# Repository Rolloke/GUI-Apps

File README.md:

# GUI-Apps
This repository contains Qt Projects for several scopes

### GitView 

App providing tools to work with git repositories.
- works with Qt5 and Qt6
- displays a tree containing files and status of files
  - visibility of the file may depend on status
- editing text files
- editing of binary files
- search of text
  - in single text
  - in textfiles contained by a selected folder and subfolders
  - in all tree views
- preview of html and markdown files
- shows difference of text files
  - supports several diff and merge tools
  - difference between branches
  - merge branches with external tools (meld, etc)
- shows history
- shows stash list
- shows blame
- shows branches

### RaspiMediaList

Kodi media list viewer and editor

- Test TV or Radio channels instantly with media viewer / player.
- supports also reply with other players like ***VLC***
- Shows media info of streamed data
  - works better with Qt5 than with Qt6
- Stores TV or Radio channels from m3u files as favorites for usage within raspberry kodi.  
- Supports upload to and download from raspberry kodi. 

### Oscilloscope 

Oscilloscope and **function** generator for selectable audio devices on sound card of a PC (Qt5)

- Calibration of single channels regarding offset and amplification
- Supports also probes with different amplification
- Support several trigger functions
- FFT with filter functions
- Mathematical function for combining channels
- Cursors

### RecentFilesList

Program to edit recent files list of Linux Ubuntu

- Opens files from List
- Removes entries from list
- Stores changed entries into list 

#### Warranty

These programs are provided AS IS with NO WARRANTY OF ANY KIND

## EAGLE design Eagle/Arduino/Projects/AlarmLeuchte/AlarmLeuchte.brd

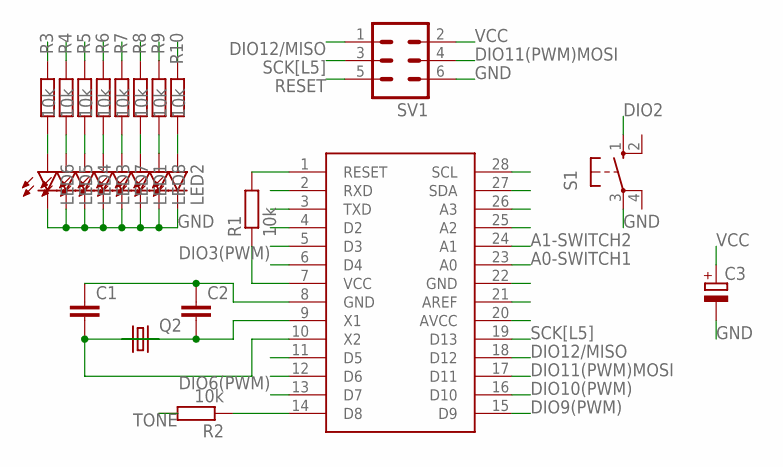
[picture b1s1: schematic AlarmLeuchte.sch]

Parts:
C1, C2: C-EU025-024X044; C025-024X044
C3: CPOL-EUE3.5-8; E3,5-8
LED1, LED2, LED3, LED4, LED5, LED6, LED7, LED8: LED5MM
Q2: CRYSTALHC49S; HC49/S
R1: 10k; 0207/15
R2, R3, R4, R5, R6, R7, R8, R9: 10k; 0207/10
R10: 10k; 0204/7
S1: 10-XX; B3F-10XX
SV1: MA03-2
U$1: ATMEGA328P-PU; DIL28-3

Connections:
A0-SWITCH1: U$1.23 (A0)
A1-SWITCH2: U$1.24 (A1)
A3: U$1.26 (A3)
A4[SDA]: U$1.27 (SDA)
A5[SCL]: R9.1, U$1.28 (SCL)
AREF: U$1.21 (AREF)
DIO1(TX): U$1.3 (TXD)
DIO2: S1.1 (S), U$1.4 (D2), U$1.25 (A2)
DIO3(PWM): R8.1, U$1.5 (D3)
DIO4: R7.1, U$1.6 (D4)
DIO5(PWM): R5.1, U$1.11 (D5)
DIO6(PWM): R10.1, U$1.12 (D6)
DIO7: R3.1, U$1.13 (D7)
DIO8: R2.1, U$1.14 (D8)
DIO9(PWM): R4.1, U$1.15 (D9)
DIO10(PWM): R6.1, U$1.16 (D10)
DIO11(PWM)MOSI: SV1.4, U$1.17 (D11)
DIO12/MISO: SV1.1, U$1.18 (D12)
DPIO0(RX): U$1.2 (RXD)
GND: C1.1, C2.1, C3.-, LED1.K (C), LED2.K (C), LED3.K (C), LED4.K (C), LED5.K (C), LED6.K (C), LED7.K (C), LED8.K (C), S1.3, SV1.6, U$1.8 (GND), U$1.22 (GND)
unnamed: LED6.A, R3.2
unnamed: LED5.A, R4.2
unnamed: LED4.A, R5.2
unnamed: LED3.A, R6.2
unnamed: LED7.A, R7.2
unnamed: LED1.A, R8.2
unnamed: LED8.A, R9.2
unnamed: LED2.A, R10.2
RESET: R1.2, SV1.5, U$1.1 (RESET)
SCK[L5]: SV1.3, U$1.19 (D13)
TONE: R2.2
VCC: C3.+, R1.1, SV1.2, U$1.7 (VCC), U$1.20 (AVCC)
X1: C2.2, Q2.1, U$1.9 (X1)
X2: C1.2, Q2.2, U$1.10 (X2)

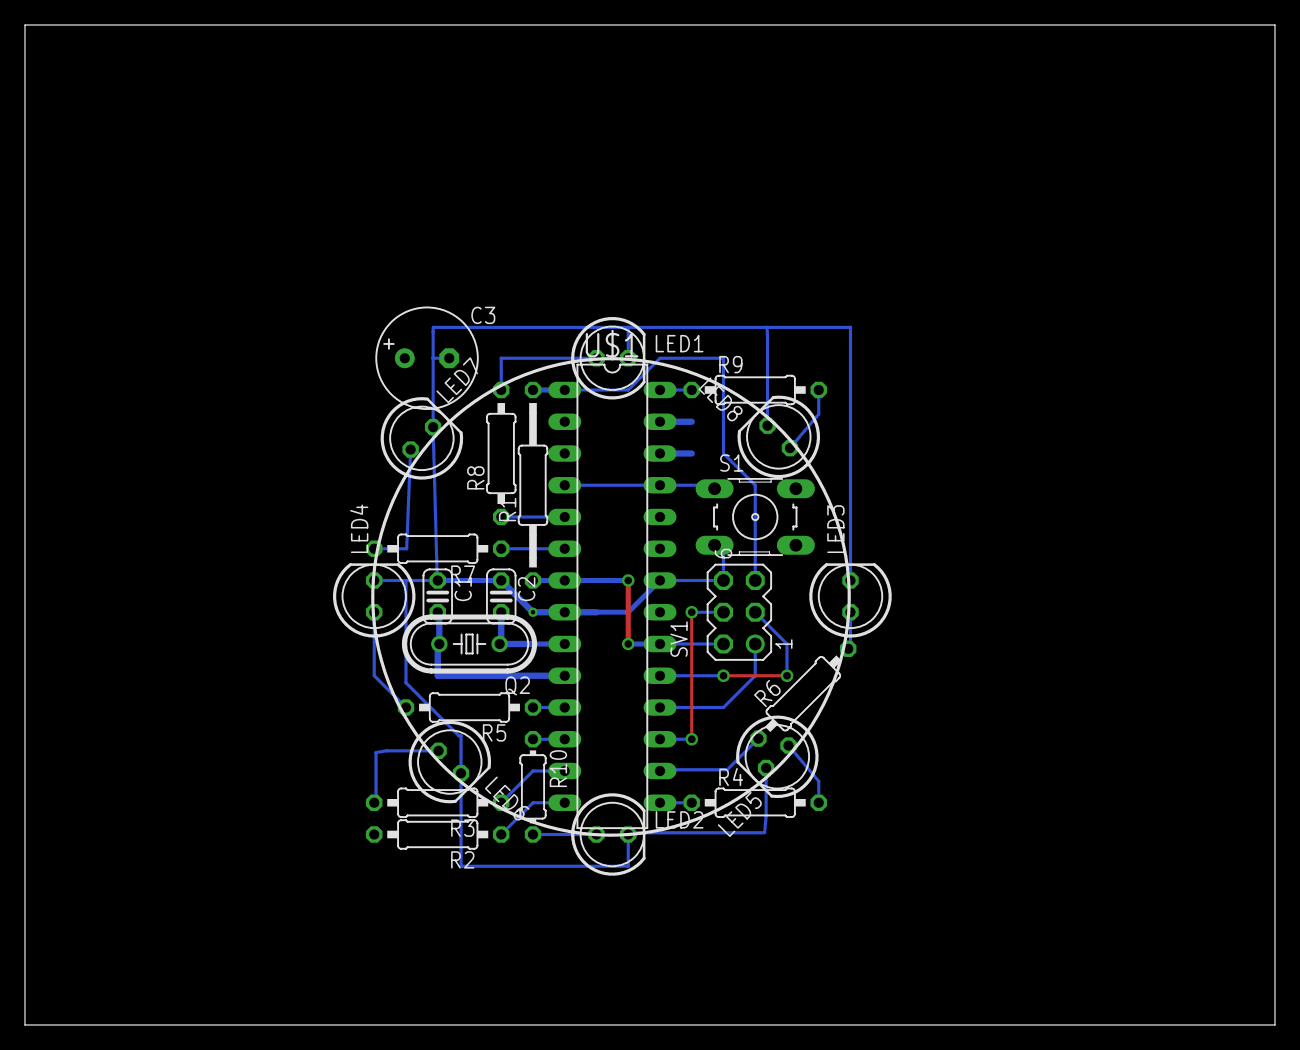
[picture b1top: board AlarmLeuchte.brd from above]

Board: 2 copper layers, 100.0 x 80.0 mm, 25 parts (0 on the bottom side), 26 nets.

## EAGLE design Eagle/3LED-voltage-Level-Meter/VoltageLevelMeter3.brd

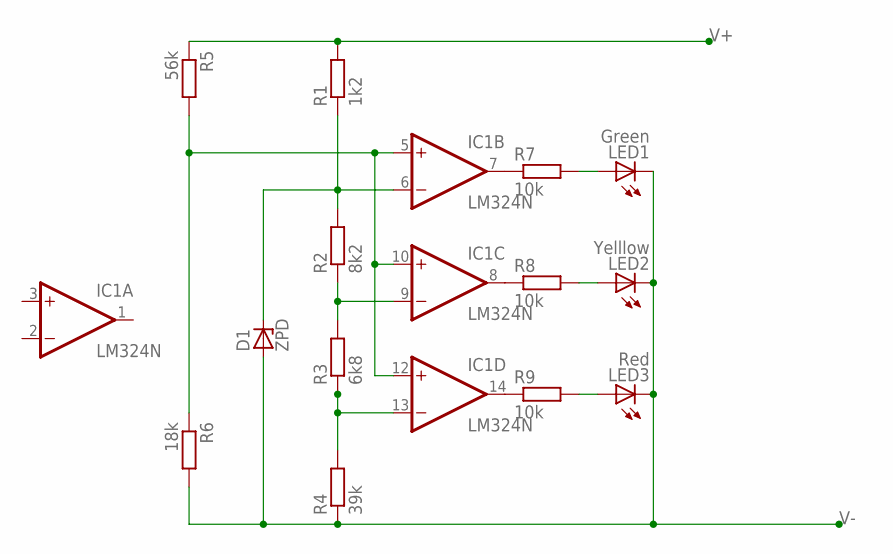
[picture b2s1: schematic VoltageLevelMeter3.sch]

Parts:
D1: ZPD; DO35Z10
IC1: LM324N; DIL14
LED1: Green; LED3MM
LED2: Yelllow; LED3MM
LED3: Red; LED3MM
R1: 1k2; 0207/7
R2: 8k2; 0207/7
R3: 6k8; 0207/7
R4: 39k; 0207/7
R5: 56k; 0207/7
R6: 18k; 0207/7
R7, R8, R9: 10k; 0207/7

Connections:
unnamed: D1.C, IC1.6 (-IN), R1.1, R2.2
unnamed: IC1.9 (-IN), R2.1, R3.2
unnamed: IC1.13 (-IN), R3.1, R4.2
unnamed: IC1.14 (OUT), R9.1
unnamed: IC1.8 (OUT), R8.1
unnamed: IC1.7 (OUT), R7.1
unnamed: IC1.5 (+IN), IC1.10 (+IN), IC1.12 (+IN), R5.2, R6.1
unnamed: LED1.A, R7.2
unnamed: LED2.A, R8.2
unnamed: LED3.A, R9.2
V+: IC1.4 (V+), R1.2, R5.1
V-: D1.A, IC1.11 (V-), LED1.K (C), LED2.K (C), LED3.K (C), R4.1, R6.2

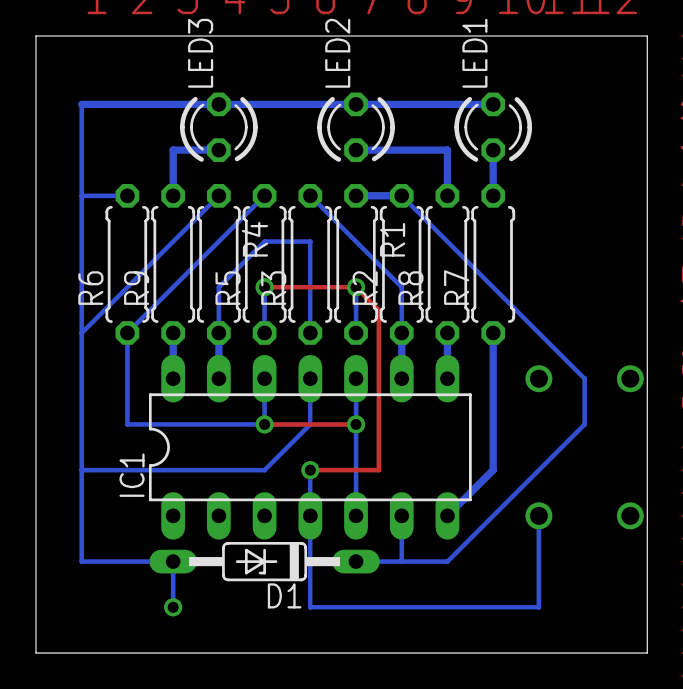
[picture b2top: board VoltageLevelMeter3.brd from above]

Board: 2 copper layers, 34.0 x 34.3 mm, 14 parts (0 on the bottom side), 12 nets.

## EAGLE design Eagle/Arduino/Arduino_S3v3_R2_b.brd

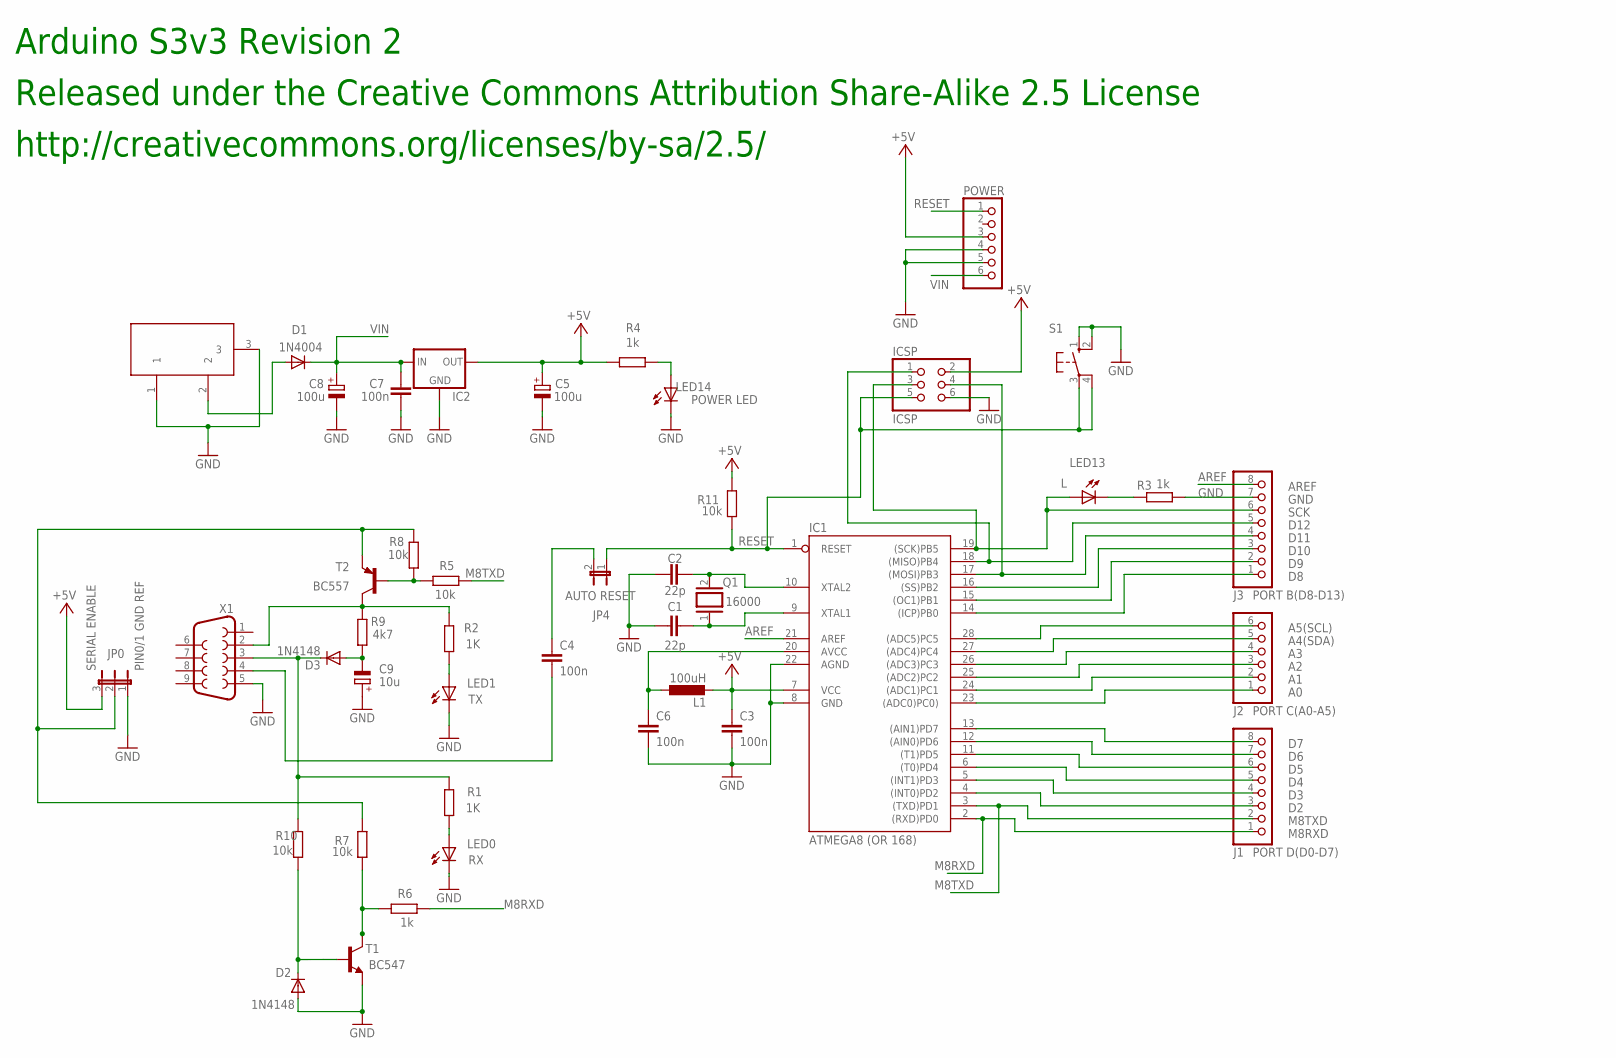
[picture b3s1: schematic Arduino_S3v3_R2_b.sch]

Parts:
C1, C2: 22p; C025-024X044
C3, C4, C6, C7: 100n; C050-025X075
C5, C8: 100u; E3,5-8
C9: 10u; E5-6
D1: 1N4004; DO41-10
D2, D3: 1N4148; DO35-10
DC1: DC21MMX; DC-21MM
IC1: ATMEGA8 (OR 168); DIL28-3
IC2: 78XXL
ICSP: ICSP; 2X03
J1: PORT D(D0-D7); 1X08
J2: PORT C(A0-A5); 1X06
J3: PORT B(D8-D13); 1X08
JP0: JP2W
JP4: AUTO RESET; JP1W
L1: 100uH; 0204/5
LED0: RX; LED3MM
LED1: TX; LED3MM
LED13: L; LED3MM
LED14: POWER LED; LED3MM
POWER: PINHD-1X6; 1X06
Q1: 16000; QS
R1, R2: 1K; 0207/10
R3, R4, R6: 1k; 0207/10
R5, R7, R8, R10, R11: 10k; 0207/10
R9: 4k7; 0207/10
S1: 10-XX; B3F-10XX
T1: BC547; TO92
T2: BC557; TO92-EBC
X1: F09H

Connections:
+5V: C3.1, C5.+, IC1.7 (VCC), IC2.OUT, ICSP.2, JP0.3, L1.2, POWER.3, R4.2, R11.2
A0: IC1.23 ((ADC0)PC0)), J2.1
A1: IC1.24 ((ADC1)PC1), J2.2
A2: IC1.25 ((ADC2)PC2), J2.3
A3: IC1.26 ((ADC3)PC3), J2.4
A4(SDA): IC1.27 ((ADC4)PC4), J2.5
A5(SCL): IC1.28 ((ADC5)PC5), J2.6
AREF: IC1.21 (AREF), J3.8
D2: IC1.4 ((INT0)PD2), J1.3
D3: IC1.5 ((INT1)PD3), J1.4
D4: IC1.6 ((T0)PD4), J1.5
D5: IC1.11 ((T1)PD5), J1.6
D6: IC1.12 ((AIN0)PD6), J1.7
D7: IC1.13 ((AIN1)PD7), J1.8
D8: IC1.14 ((ICP)PB0), J3.1
D9: IC1.15 ((OC1)PB1), J3.2
D10: IC1.16 ((SS)PB2), J3.3
D11: IC1.17 ((MOSI)PB3), ICSP.4, J3.4
D12: IC1.18 ((MISO)PB4), ICSP.1, J3.5
GND: C1.1, C2.1, C3.2, C5.-, C6.2, C7.1, C8.-, C9.+, D2.A, DC1.1, DC1.3, IC1.8 (GND), IC1.22 (AGND), IC2.GND, ICSP.6, J3.7, JP0.1, LED0.K (C), LED1.K (C), LED14.K (C), POWER.4, POWER.5, R3.1, S1.1 (S), S1.2 (S1), T1.1 (E), X1.5
M8RXD: IC1.2 ((RXD)PD0), J1.1, R6.1
M8TXD: IC1.3 ((TXD)PD1), J1.2, R5.1
unnamed: C9.-, D3.A, R9.1
unnamed: LED14.A, R4.1
unnamed: C1.2, IC1.9 (XTAL1), Q1.1
unnamed: C2.2, IC1.10 (XTAL2), Q1.2
unnamed: D1.A, DC1.2
unnamed: D3.C, R1.2, R10.2, X1.3
unnamed: R6.2, R7.1, T1.3 (C)
unnamed: R5.2, R8.2, T2.B
unnamed: D2.C, R10.1, T1.2 (B)
unnamed: LED13.K (C), R3.2
unnamed: LED1.A, R2.1
unnamed: LED0.A, R1.1
unnamed: C4.1, JP4.2
unnamed: C4.2, X1.4
unnamed: R2.2, R9.2, T2.C, X1.2
unnamed: C6.1, IC1.20 (AVCC), L1.1
RESET: IC1.1 (RESET), ICSP.5, JP4.1, POWER.1, R11.1, S1.3, S1.4 (P1)
SCK: IC1.19 ((SCK)PB5), ICSP.3, J3.6, LED13.A
SERIAL_VCC: JP0.2, R7.2, R8.1, T2.E
VIN: C7.2, C8.+, D1.C, IC2.IN, POWER.6

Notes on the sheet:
PIN0/1 GND REF
SERIAL ENABLE
Released under the Creative Commons Attribution Share-Alike 2.5 License
http://creativecommons.org/licenses/by-sa/2.5/
Arduino S3v3 Revision 2

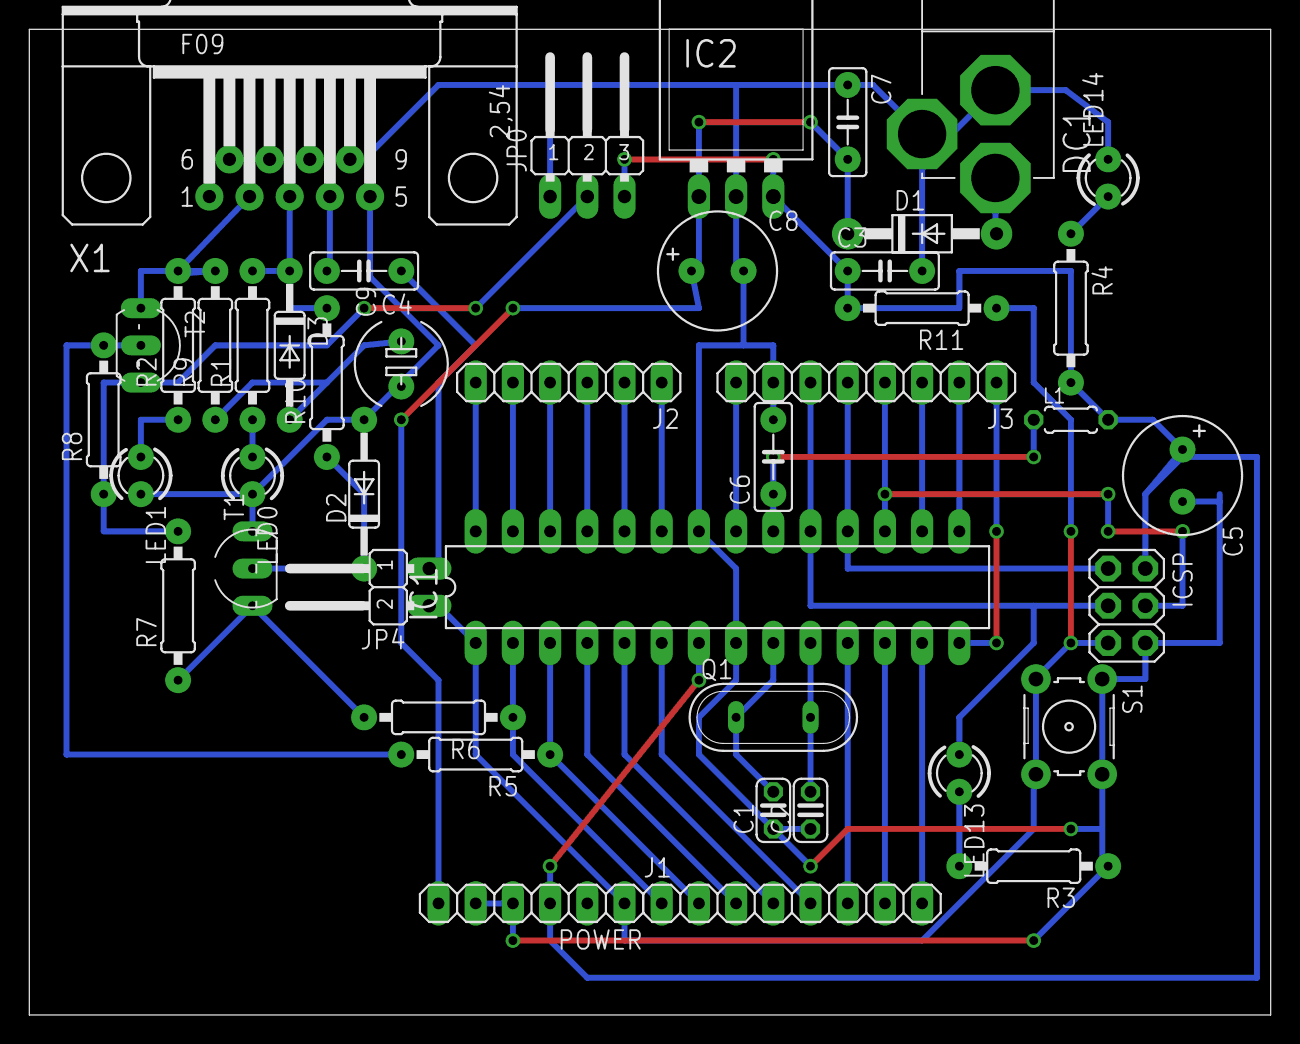
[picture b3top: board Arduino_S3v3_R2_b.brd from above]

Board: 2 copper layers, 84.8 x 67.3 mm, 43 parts (0 on the bottom side), 42 nets.

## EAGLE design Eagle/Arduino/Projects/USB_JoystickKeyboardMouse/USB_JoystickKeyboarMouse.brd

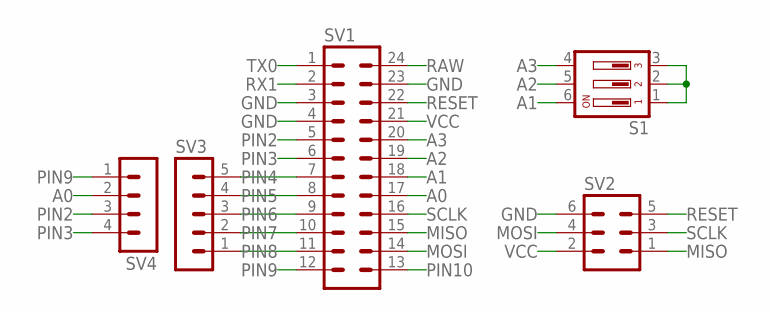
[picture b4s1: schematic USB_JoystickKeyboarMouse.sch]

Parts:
S1: DIP03YL
SV1: IC24P
SV2: MA03-2
SV3: MA05-1
SV4: MA04-1

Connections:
A0: SV1.17, SV4.2
A1: S1.6, SV1.18
A2: S1.5, SV1.19
A3: S1.4, SV1.20
GND: S1.1, S1.2, S1.3, SV1.3, SV1.4, SV1.23, SV2.6
MISO: SV1.15, SV2.1
MOSI: SV1.14, SV2.4
PIN2: SV1.5, SV4.3
PIN3: SV1.6, SV4.4
PIN4: SV1.7, SV3.5
PIN5: SV1.8, SV3.4
PIN6: SV1.9, SV3.3
PIN7: SV1.10, SV3.2
PIN8: SV1.11, SV3.1
PIN9: SV1.12, SV4.1
PIN10: SV1.13
RAW: SV1.24
RESET: SV1.22, SV2.5
RX1: SV1.2
SCLK: SV1.16, SV2.3
TX0: SV1.1
VCC: SV1.21, SV2.2

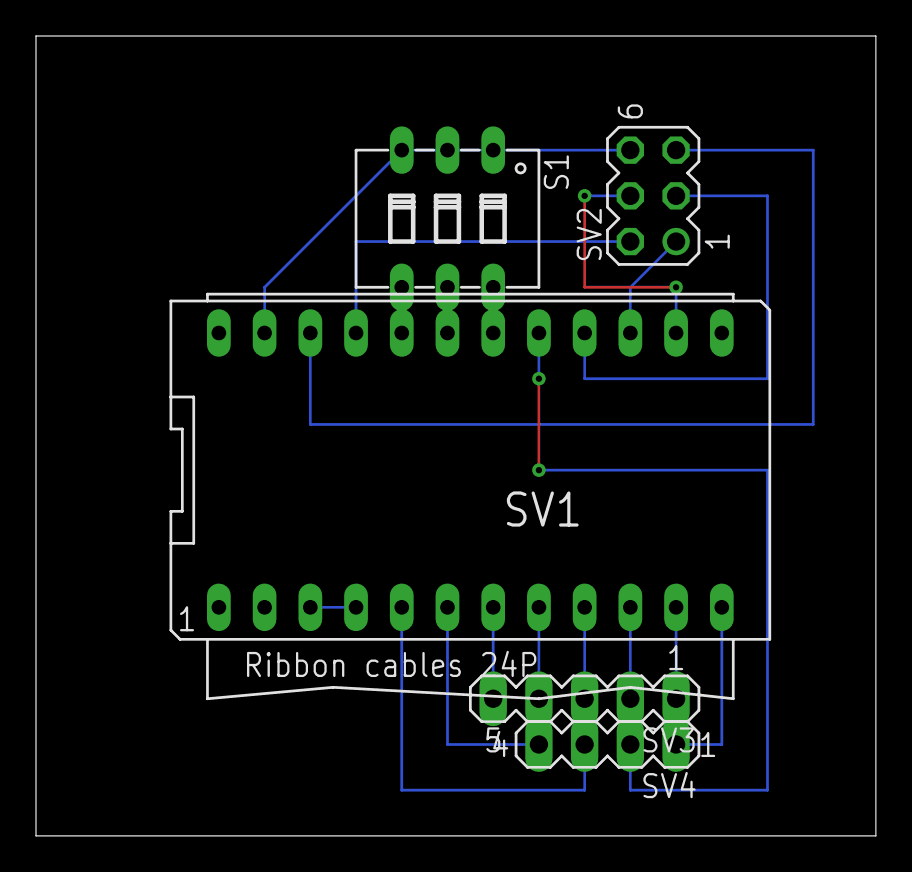
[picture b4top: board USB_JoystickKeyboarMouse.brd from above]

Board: 2 copper layers, 46.7 x 44.4 mm, 5 parts (0 on the bottom side), 18 nets.

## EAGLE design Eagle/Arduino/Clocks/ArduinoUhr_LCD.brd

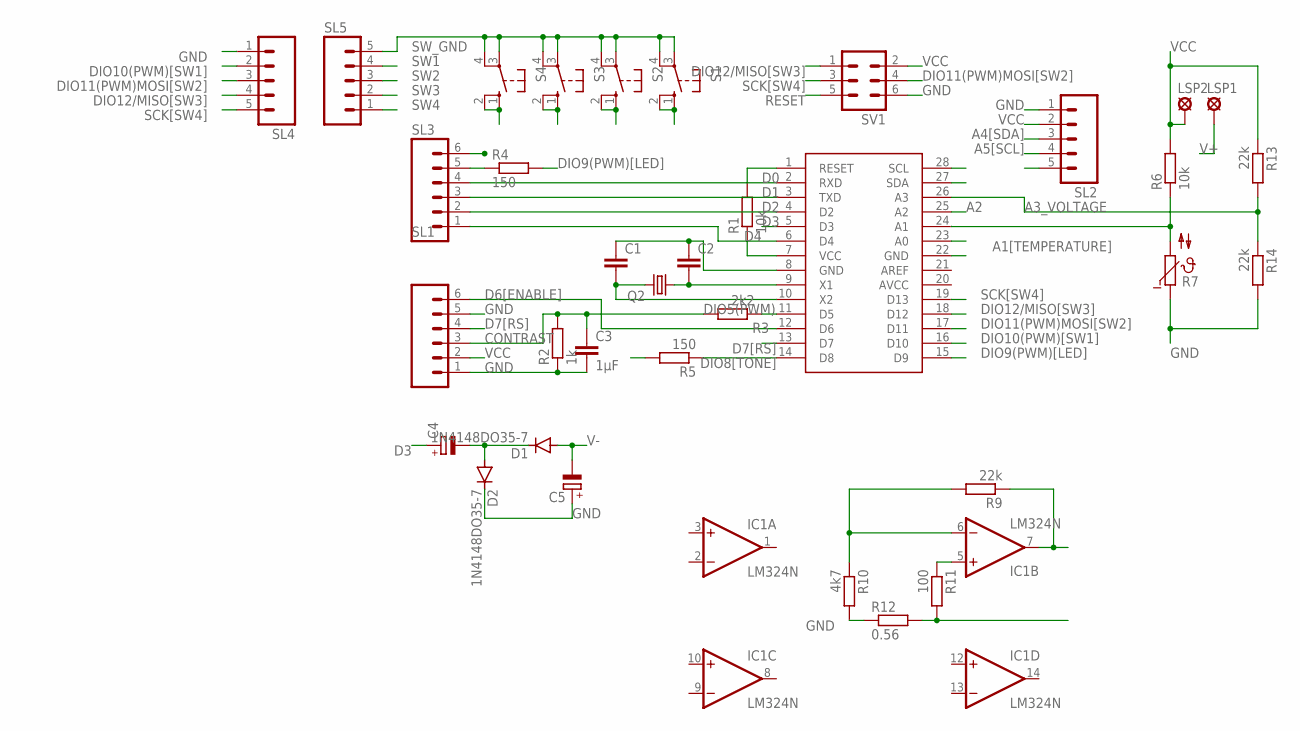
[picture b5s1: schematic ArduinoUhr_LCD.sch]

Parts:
C1, C2: C-EU025-024X044; C025-024X044
C3: 1µF; C050-024X044
C4, C5: CPOL-EUE2-5; E2-5
D1, D2: 1N4148DO35-7; DO35-7
IC1: LM324N; DIL14
LSP1, LSP2: LSP10
Q2: CRYSTALHC49S; HC49/S
R1: 10k; 0207/15
R2: 1k; 0204/7
R3: 2k2; 0204/7
R4: 150; 0207/10
R5: 150; 0204/7
R6: 10k; 0207/10
R7: NTC640-9; N640
R9, R13, R14: 22k; 0204/7
R10: 4k7; 0204/7
R11: 100; 0204/7
R12: 0.56; P0613/15
S1, S2, S3, S4: 10-XX; B3F-10XX
SL1, SL3: M06; 06P
SL2, SL4, SL5: M05; 05P
SV1: MA03-2
U$1: ATMEGA328P-PU; DIL28-3

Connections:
A0[CURRENT]: IC1.7 (OUT), R9.1, U$1.23 (A0)
A1[TEMPERATURE]: R6.1, R7.2, U$1.24 (A1)
A2: U$1.25 (A2)
A3_VOLTAGE: R13.2, R14.1, U$1.26 (A3)
A4[SDA]: SL2.3, U$1.27 (SDA)
A5[SCL]: SL2.4, U$1.28 (SCL)
CONTRAST: C3.1, R2.2, R3.2, SL1.3
D0: SL3.4, U$1.2 (RXD)
D1: SL3.3, U$1.3 (TXD)
D2: SL3.2, U$1.4 (D2)
D3: C4.+, U$1.5 (D3)
D4: SL3.1, U$1.6 (D4)
D6[ENABLE]: SL1.6, U$1.12 (D6)
D7[RS]: SL1.4, U$1.13 (D7)
DIO5(PWM): R3.1, U$1.11 (D5)
DIO8[TONE]: R5.1, U$1.14 (D8)
DIO9(PWM)[LED]: R4.2, U$1.15 (D9)
DIO10(PWM)[SW1]: SL4.2, U$1.16 (D10)
DIO11(PWM)MOSI[SW2]: SL4.3, SV1.4, U$1.17 (D11)
DIO12/MISO[SW3]: SL4.4, SV1.1, U$1.18 (D12)
GND: C1.1, C2.1, C3.2, C5.+, D2.C, R2.1, R7.1, R10.2, R12.1, R14.2, SL1.1, SL1.5, SL2.1, SL3.6, SL4.1, SV1.6, U$1.8 (GND), U$1.22 (GND)
unnamed: IC1.6 (-IN), R9.2, R10.1
unnamed: R4.1, SL3.5
unnamed: C4.-, D1.C, D2.A
unnamed: IC1.5 (+IN), R11.1
unnamed: R11.2, R12.2
RESET: R1.2, SV1.5, U$1.1 (RESET)
SCK[SW4]: SL4.5, SV1.3, U$1.19 (D13)
SW1: S4.1 (S), S4.2 (S1), SL5.4
SW2: S3.1 (S), S3.2 (S1), SL5.3
SW3: S2.1 (S), S2.2 (S1), SL5.2
SW4: S1.1 (S), S1.2 (S1), SL5.1
SW_GND: S1.3, S1.4 (P1), S2.3, S2.4 (P1), S3.3, S3.4 (P1), S4.3, S4.4 (P1), SL5.5
TONE: R5.2
V+: IC1.4 (V+), LSP1.MP
V-: C5.-, D1.A, IC1.11 (V-)
VCC: LSP2.MP, R1.1, R6.2, R13.1, SL1.2, SL2.2, SV1.2, U$1.7 (VCC)
X1: C2.2, Q2.1, U$1.9 (X1)
X2: C1.2, Q2.2, U$1.10 (X2)

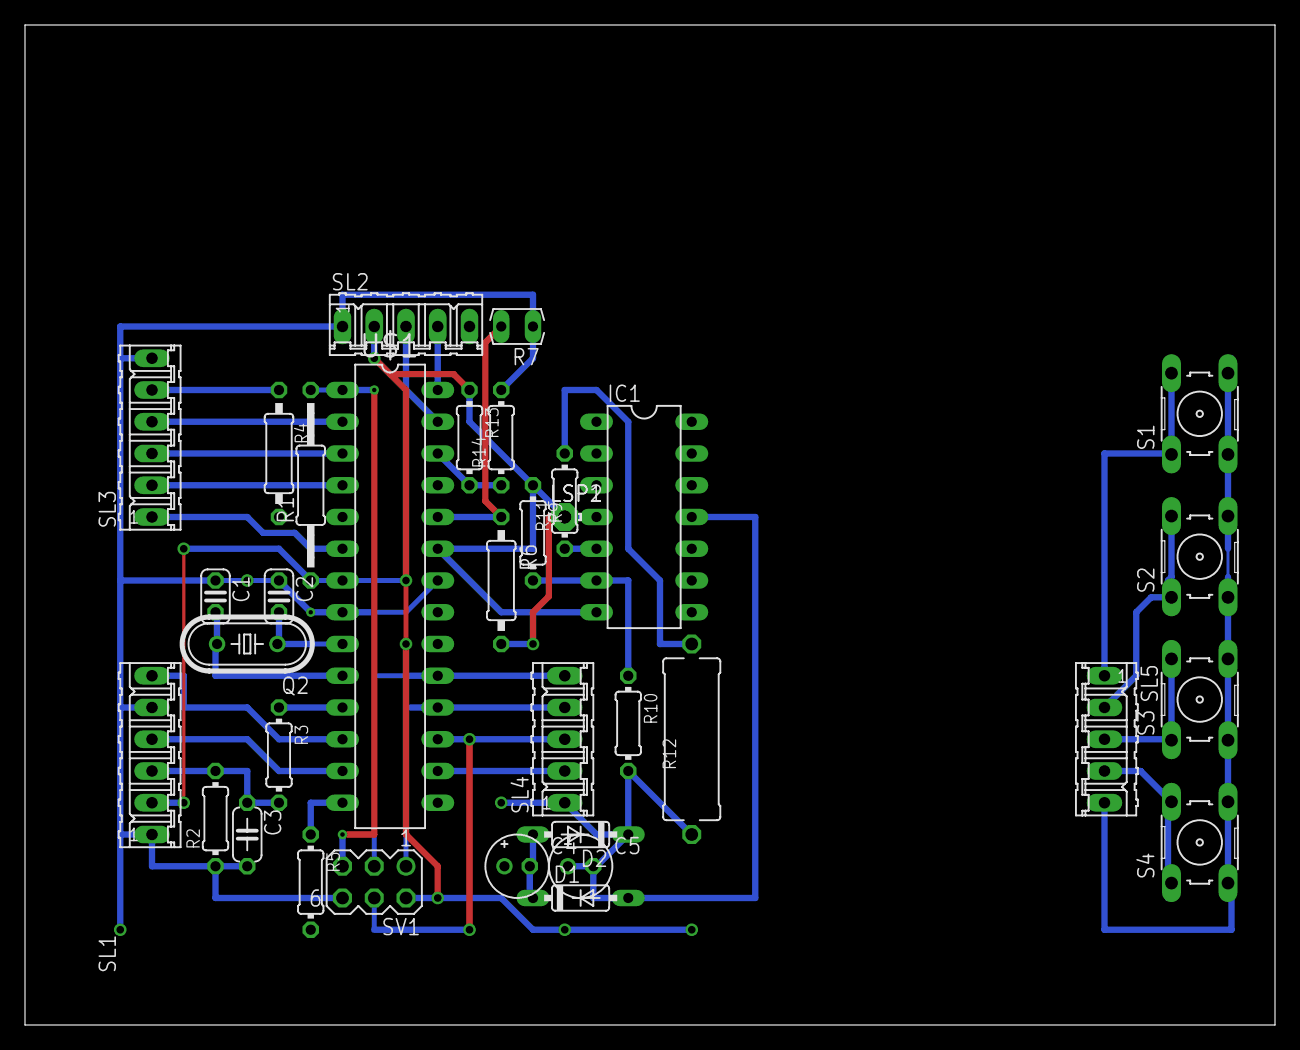
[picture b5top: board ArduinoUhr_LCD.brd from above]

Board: 2 copper layers, 100.0 x 80.0 mm, 35 parts (0 on the bottom side), 37 nets.

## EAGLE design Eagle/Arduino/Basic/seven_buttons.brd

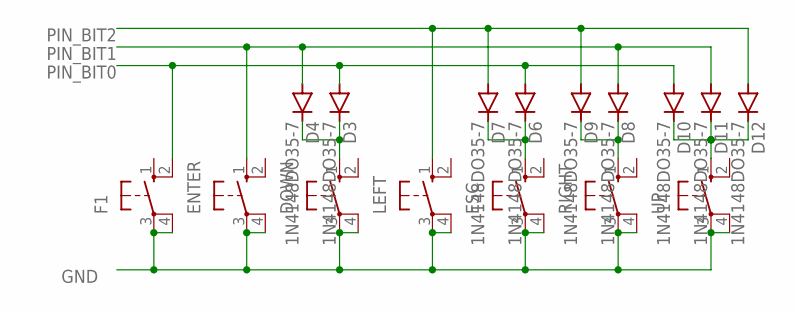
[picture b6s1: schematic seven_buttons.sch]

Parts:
D3, D4, D6, D7, D8, D9, D10, D11, D12: 1N4148DO35-7; DO35-7
DOWN: 10-XX; B3F-10XX
ENTER: 10-XX; B3F-10XX
ESC: 10-XX; B3F-10XX
F1: 10-XX; B3F-10XX
LEFT: 10-XX; B3F-10XX
RIGHT: 10-XX; B3F-10XX
UP: 10-XX; B3F-10XX

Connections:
GND: DOWN.3, DOWN.4 (P1), ENTER.3, ENTER.4 (P1), ESC.3, ESC.4 (P1), F1.3, F1.4 (P1), LEFT.3, LEFT.4 (P1), RIGHT.3, RIGHT.4 (P1), UP.3, UP.4 (P1)
unnamed: D3.C, D4.C, DOWN.1 (S)
unnamed: D6.C, D7.C, ESC.1 (S)
unnamed: D8.C, D9.C, RIGHT.1 (S)
unnamed: D10.C, D11.C, D12.C, UP.1 (S)
PIN_BIT0: D3.A, D6.A, D10.A, F1.2 (S1)
PIN_BIT1: D4.A, D8.A, D11.A, ENTER.1 (S)
PIN_BIT2: D7.A, D9.A, D12.A, LEFT.1 (S)

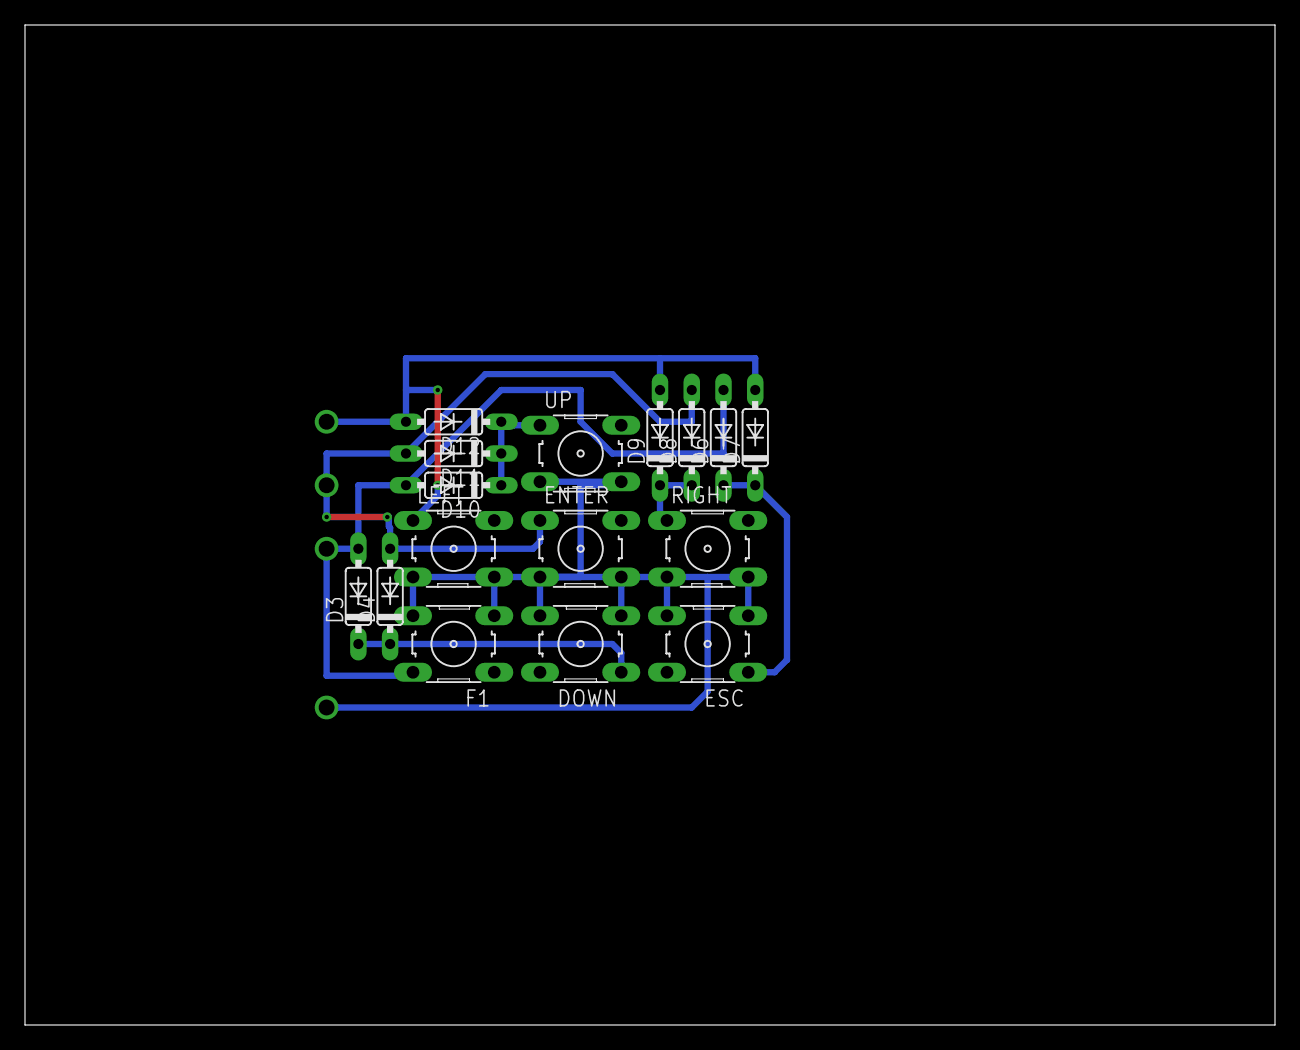
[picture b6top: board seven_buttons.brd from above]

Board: 2 copper layers, 100.0 x 80.0 mm, 16 parts (0 on the bottom side), 8 nets.

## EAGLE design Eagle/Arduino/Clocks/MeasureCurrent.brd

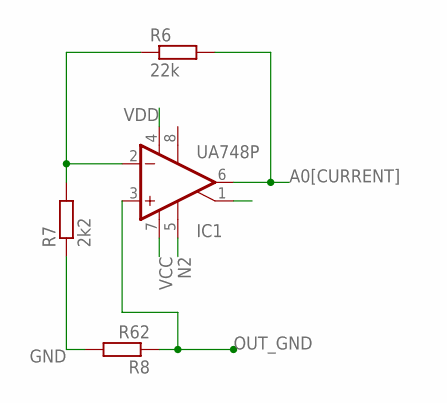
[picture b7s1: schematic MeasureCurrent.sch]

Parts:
IC1: UA748P; DIL08
R6: 22k; 0207/12
R7: 2k2; 0207/12
R8: R62; 0207/15

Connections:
-IN: IC1.2 (-IN), R6.1, R7.2
A0[CURRENT]: IC1.6 (OUT), R6.2
GND: R7.1, R8.2
N2: IC1.5 (ON)
OUT_GND: IC1.3 (+IN), R8.1
VCC: IC1.7 (V+)
VDD: IC1.4 (V-)

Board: 2 copper layers, 4 parts (0 on the bottom side), 4 nets, no tracks yet.

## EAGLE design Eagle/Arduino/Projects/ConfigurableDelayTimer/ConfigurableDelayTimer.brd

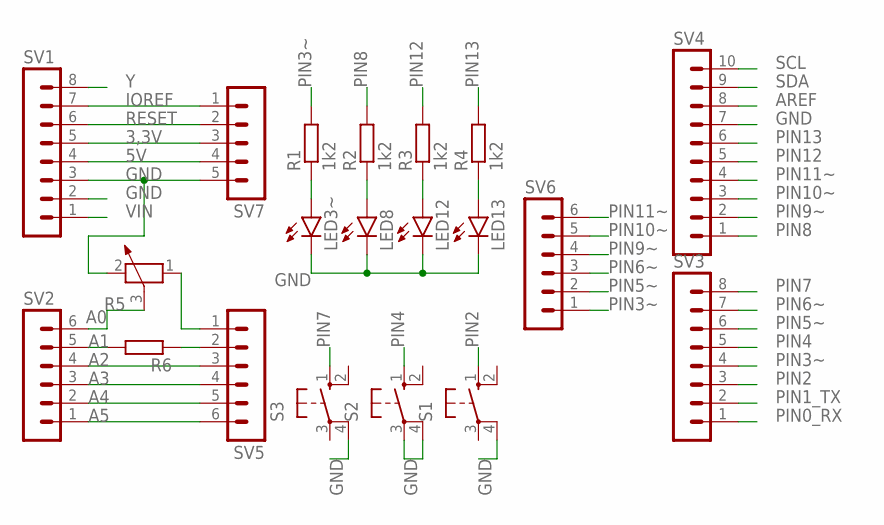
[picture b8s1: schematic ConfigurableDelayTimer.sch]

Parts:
LED3~, LED8, LED12, LED13: LED5MM
R1, R2, R3, R4: 1k2; 0207/7
R5: POTENTIOMETER_PT-10; PT-10
R6: R-EU_0207/2V; 0207/2V
S1, S2, S3: 40-XX; B3F-40XX
SV1, SV3: MA08-1
SV2, SV5, SV6: MA06-1
SV4: MA10-1
SV7: MA05-1

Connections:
3,3V: SV1.5, SV7.3
5V: SV1.4, SV7.4
A0: R5.3, SV2.6
A1: R6.2, SV2.5
A2: SV2.4, SV5.3
A3: SV2.3, SV5.4
A4: SV2.2, SV5.5
A5: SV2.1, SV5.6
AREF: SV4.8
GND: LED3~.K (C), LED8.K (C), LED12.K (C), LED13.K (C), R5.2, S1.4 (P1), S2.3, S2.4 (P1), S3.4 (P1), SV1.2, SV1.3, SV4.7, SV7.5
IOREF: SV1.7, SV7.1
unnamed: LED3~.A, R1.1
unnamed: LED8.A, R2.1
unnamed: LED12.A, R3.1
unnamed: LED13.A, R4.1
unnamed: R5.1, SV5.1
unnamed: R6.1, SV5.2
PIN0_RX: SV3.1
PIN1_TX: SV3.2
PIN2: S1.1 (S), SV3.3
PIN3~: R1.2, SV3.4, SV6.1
PIN4: S2.1 (S), SV3.5
PIN5~: SV3.6, SV6.2
PIN6~: SV3.7, SV6.3
PIN7: S3.1 (S), SV3.8
PIN8: R2.2, SV4.1
PIN9~: SV4.2, SV6.4
PIN10~: SV4.3, SV6.5
PIN11~: SV4.4, SV6.6
PIN12: R3.2, SV4.5
PIN13: R4.2, SV4.6
RESET: SV1.6, SV7.2
SCL: SV4.10
SDA: SV4.9
VIN: SV1.1
Y: SV1.8

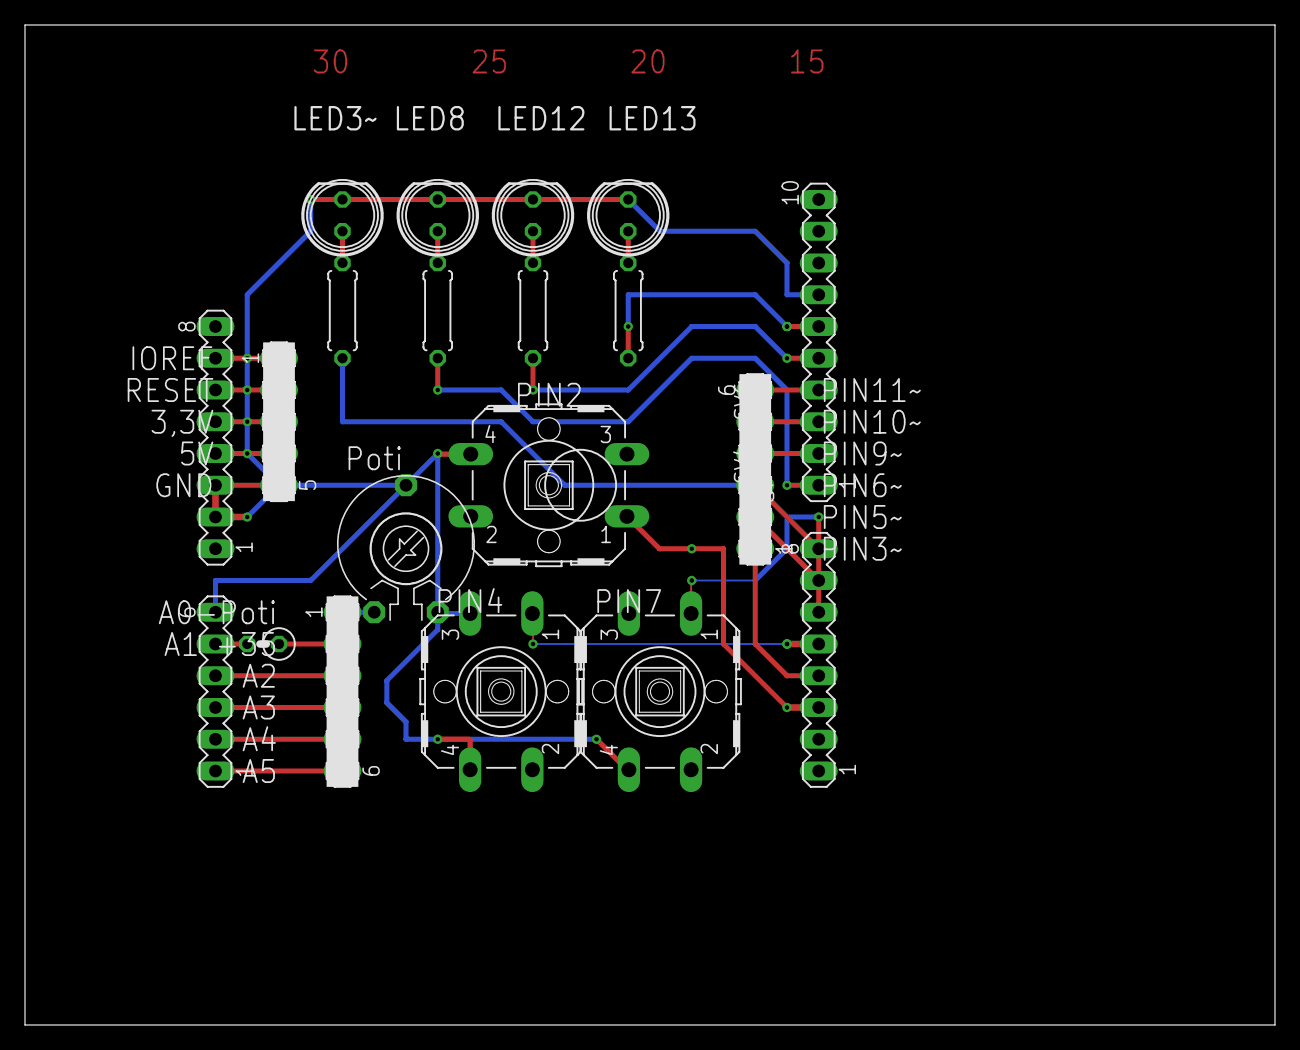
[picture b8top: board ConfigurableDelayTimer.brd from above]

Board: 2 copper layers, 100.0 x 80.0 mm, 20 parts (0 on the bottom side), 29 nets.

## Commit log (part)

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2023-10-29 modified info box text
2023-10-29 changed resize of table content
2023-10-29 try it on windows
2023-10-31 implemented encoding for Qt6
2023-11-01 fixed testcode
2023-11-03 custom action enable status
2023-11-07 added sample json files
2023-11-07 added sample m3u files for media player
2023-11-07 implemented html and markdown preview using qtextbrowser
2023-11-08 icons and fixes
2023-11-08 icon and message
2023-11-10 changed preview behaviour of text editor
2023-11-13 improved batch command behaviour
2023-11-18 qt version makros
2023-11-19 resize index vector
2023-11-26 improve file open stuff
2023-11-27 changed qt version dependency
2023-11-27 changed language model file
2023-12-03 change read text of temp file
2023-12-03 fixe branch cmd on windows
2023-12-04 added format for permission
2023-12-06 close tempfile to open new file
2023-12-10 improved binary view
2023-12-11 new git higlighter item, filter browser output
2023-12-17 added dark palette editor and fixed bugs
2023-12-19 added palettecolorselector
2023-12-19 repaired go language definition
2023-12-30 version dependency
2023-12-31 compatibility
2023-12-31 added randomgenerator
2023-12-31 added logo
2024-01-09 added script
2024-01-19 tab text indent separate name and tooltip for action in config
2024-01-25 fixed background activity behaviour
2024-02-23 additional background command text view
2024-02-25 arduino unittest fixes
2024-02-25 fix switch off 2 output window
2024-02-26 changed get() to data()
2024-02-26 fixes from work test
2024-02-26 refactured code
2024-02-27 fixes from work test 2
2024-02-28 fixed depricated and empty history file name
2024-03-10 clear background process log
2024-03-10 set focus in find text edit control
2024-03-11 some comments
2024-03-15 activated simd
2024-03-17 split view and simd
2024-03-17 add simd
2024-03-20 simplified find all
2024-03-22 simd ideas
2024-03-24 implemented other data types for simd
2024-03-25 in out with other type and with limit AVX2 512 test
2024-03-27 compile avx512 works but programm crashes
2024-04-01 some intel stuff
2024-04-02 implemented 256 intrinsic
2024-04-05 fixed fast search from Samuel
2024-04-11 improved splitter windows
2024-04-12 simd improved
2024-04-16 trigonometric test
2024-04-27 improved focus control of text windows
2024-05-19 view management rename untracked files
2024-05-19 added shortcut keys mode to get by press key
2024-05-20 improved shortcut keys for custom commands
2024-05-20 improve more
2024-05-31 several changes
2024-06-03 shortcut improved
2024-06-06 desktop file for oscope
2024-06-15 comment
2024-06-16 improvements regarding html and media
2024-06-19 window focus control edit files reload only on command update double click only show file without reload Navigation links open in extra browser
2024-06-30 improved functions - browser and markdown preview links - qt6 mediainformation
2024-06-30 added input dialog
2024-07-11 execute command in text line to text viewer
2024-07-12 used variadic compare functions
2024-07-13 range based loop approvements
2024-07-13 varaiadic xor
2024-07-14 word wrap for text editor
2024-07-16 fixed close window command
2024-07-17 Fixed edit message box text for commands
2024-07-22 update Stash list
2024-07-26 update stash list after stash commands
2024-08-08 store commands in separate file
2024-09-20 added kodinerds link to raspimedialist
2024-09-22 diff branch improved
2024-09-24 Update customgitactions.cpp
    added comment
2024-09-27 Update qstashtreewidget.cpp
    prohibit abbreviated names in stash file list
2024-10-13 implemented miscelaneous item editor
2024-10-15 logging severity
2024-10-18 regard repository within worker command
2024-10-22 optional usage of boost
2024-10-23 mime type windows
2024-10-28 sort order of history
2024-10-31 qt6 depricated issues
2024-10-31 fixed metadata retreival for mediaplayer
2024-11-06 linux themes enumerated
2024-11-17 icon for misc settings menu
2024-11-17 remove window specific code
2024-11-18 read folders with media content in raspimedialist
2024-11-20 enhance media player
2024-11-24 read media files
2024-11-24 update media information for player
2024-11-25 update position
2024-11-30 improved behaviour of raspimedialist
2024-12-07 Ã¶ffnen von mediafiles unter windows, typo
2024-12-08 things todo
2024-12-08 fixed various issues - stash view double entries - update repository sub folder
2024-12-20 update folder
2024-12-25 include missing header
2025-01-08 optimize regular expression use
2025-01-15 some fixes for raspi media list
2025-01-15 prohibit builtin key commands
2025-01-20 remove wrong include
2025-02-15 RepositoryView column settings
2025-02-16 qt6 enabled
2025-02-19 select open file as auto, text, binary
2025-02-21 add command compare to menu
2025-03-03 git clone in thread, raspi media player separation of functions
2025-03-17 raspi media list fixes
2025-03-17 Ideas and fixes
2025-03-19 added functionality close all files of repo, when repo is closed
2025-03-28 evaluate Return in find edit and trigger Execute button
2025-03-30 fix binary file issues for edit, store, display in table
2025-04-02 Update mainwindow.cpp
    Fixed Command ID MergeTwoBranches for create action
2025-04-02 check pointer before access
2025-04-03 add merge command
2025-04-04 features find, execute with return font up/dow with actions
2025-04-05 fixed recent files bug
2025-04-07 added goto line and execute cmd
2025-04-08 alternative to variadic templates
2025-04-09 improved history view
2025-04-14 implemented history graph for git
2025-04-15 improve drawing of graph
2025-04-16 Create README.md
    first file
2025-04-16 Create LICENSE.md
    license and copyright
2025-04-16 added GitView to GUI-Apps
2025-04-16 added RaspiMediaList to GUI-Apps
2025-04-16 added Oscilloscope to GUI-Apps
2025-04-17 fix depricated things
2025-04-17 make compileable
2025-04-17 added cmake files
2025-04-22 implemented cmake files for all projects
2025-04-22 added recent files list
2025-04-22 edetied readme
2025-04-27 execute in selected folder
2025-05-25 implemented hideable test sections
2025-05-26 show or hide all sections
2025-05-27 set nested sections to parent section visibility
2025-06-10 codereview and bugfix
2025-06-14 goto line and textcodec qt6 compatibility
2025-06-15 sync from public proj
2025-06-15 show text block info
2025-06-28 qt 5 compatibility for qt6 removed graphics history display
2025-06-29 improve windows functions
2025-07-02 git diff --name-only improved
2025-07-07 got to section end or begin
2025-07-07 suppress mouse release event to prvent from draw twice
2025-07-09 improved download of m3u files
2025-07-11 compatibility isues
2025-07-12 Add Core5Compat
2025-07-21 remove repository depending tree entries
2025-07-22 removed unused things
2025-07-22 show also ignored files in repo
2025-07-27 added git reset commands
2025-09-22 parse output text for bookmarks
2025-09-22 add outputparser
2025-09-23 column resize
2025-09-27 list branches at open repo
2025-10-09 dont save binary view when save all
2025-10-13 implemented branch command and show unused commands
2025-10-14 test
2025-10-18 refactor and fix
2025-11-01 try to store and restore inddex list of tree
2025-11-03 implement new function
2025-11-03 implemented new function
2025-11-03 refactoring
2025-11-03 refacto
2025-11-09 submenus at intialization, update repository with restor tree states
2025-11-21 implemented reload all
2025-11-28 try to fix screen position
2025-12-01 move menues or widgets on other screens
2025-12-06 render text files in md or htm
2025-12-07 system tray message
2025-12-09 fixed focus problem
2025-12-12 contextmenue for move widgets
2025-12-14 changed som checkbox items to bool and moved to misc settings
2025-12-16 added captions to misc list
2026-01-02 implemented another yaml to read modbus values
2026-01-02 define labels
2026-01-03 read and write values checkboxes on same height
2026-01-04 implemented tabel for scheduled values
2026-01-05 resize control tab
2026-01-06 implemented button controls
2026-01-07 refactoring and bugfixing
2026-01-09 refactured and improved
2026-01-10 edit values, add control values
2026-01-15 edit chracteristic first draft
2026-01-16 refactored, double click history selects file in source tree
2026-01-20 show characteristic
2026-01-25 more values
2026-01-25 bugfixing, robustnes
2026-01-28 added a plot view and some other features
2026-01-28 improve graphics view
2026-01-29 refactured plot view
2026-01-30 plot settings and yaml entries added
2026-02-06 refactored
2026-02-07 implemented copy files on drag and drop
2026-02-07 reviewed and refactored
2026-02-08 initialization of gitview layout at first start
2026-02-10 fixed window incompatibility
2026-02-13 key change for history tree view
2026-02-20 execute commands in background, store and read bookmarks
2026-02-23 fixed bookmark storing for windoof
2026-02-24 secure handling of backgound view
2026-02-25 copy under windows
2026-02-27 window copy of files and folder fixed
2026-03-11 comment and refacturing
2026-03-20 markdown format and docu
2026-03-26 about page resizeable
2026-04-01 fixed bug for level of tree iteration
2026-04-04 Import export custom commands
2026-04-07 cascaded menus
2026-04-12 fixed remove cmd bug, icons and texts and menues
2026-04-12 icons
2026-04-12 submenues
2026-04-19 some fixes
2026-04-23 kill background task with name and pid in dialog with checkboxes
2026-04-24 created checkbox dialog function
2026-04-26 fix checkbox dialog
